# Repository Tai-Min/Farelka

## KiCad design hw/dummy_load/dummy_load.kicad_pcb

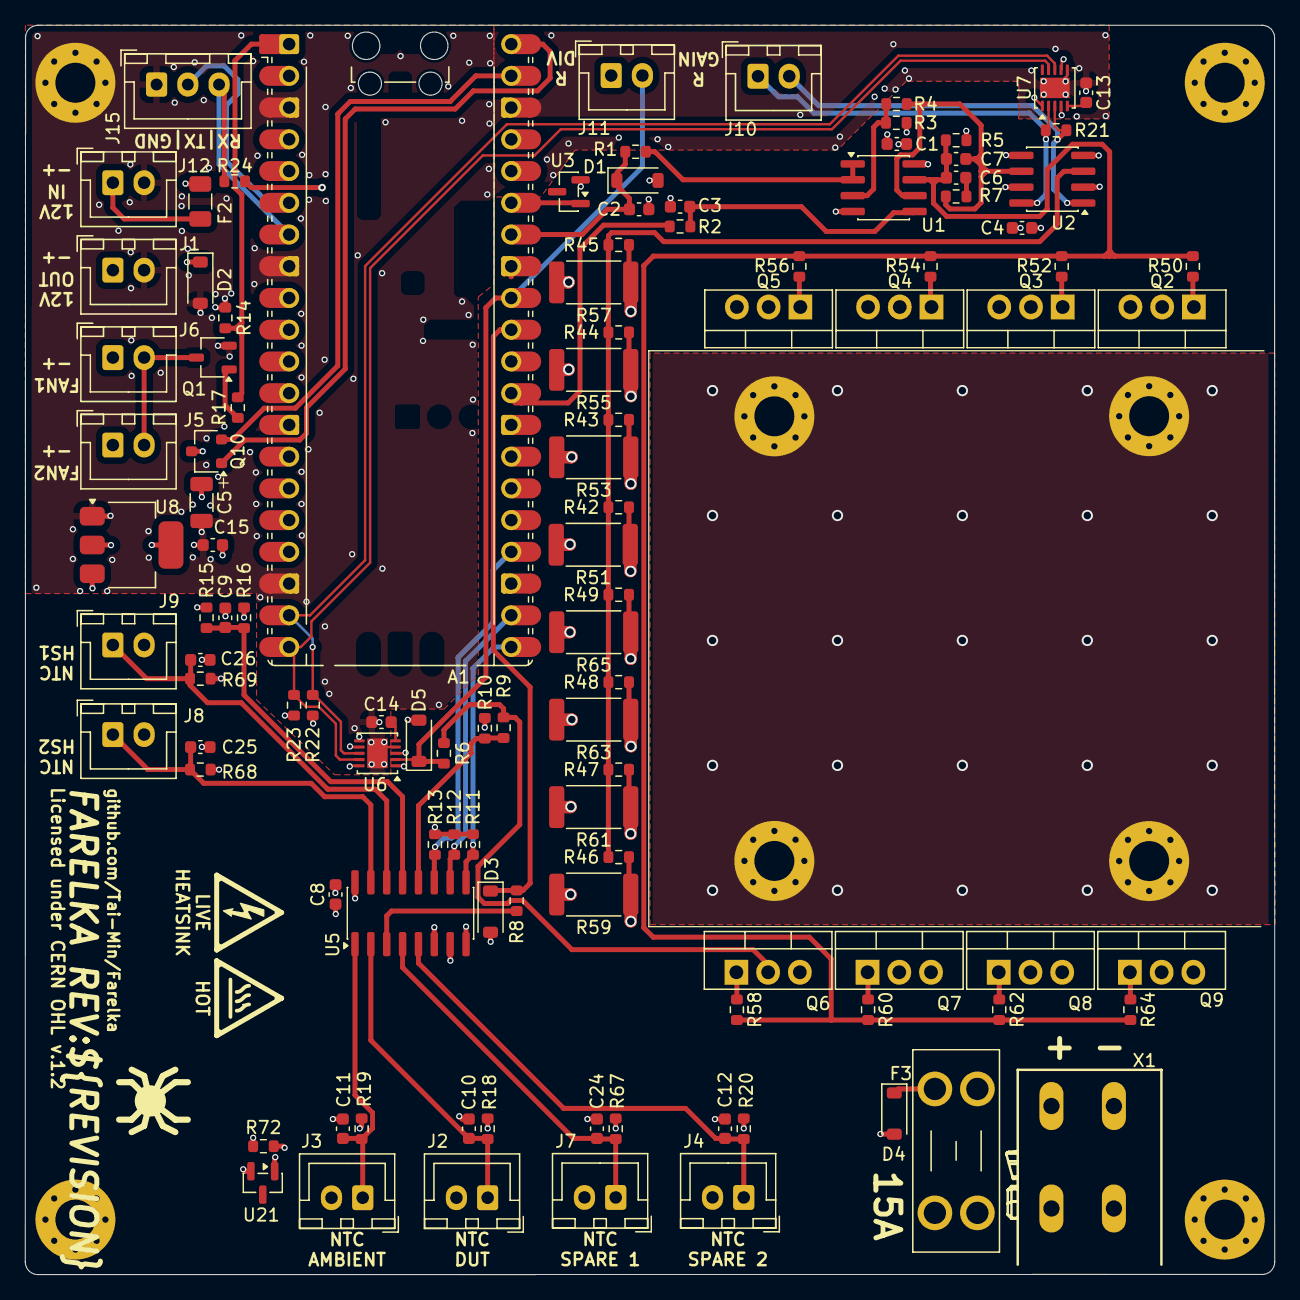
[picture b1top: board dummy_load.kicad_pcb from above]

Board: 4 copper layers, 100.0 x 100.0 mm, 115 parts (0 on the bottom side), 62 nets.

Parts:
A1: RaspberryPi_Pico; RaspberryPi_Pico_Common_Unspecified
C1, C4, C8: 100n; C_0603_1608Metric
C2, C3, C9, C10, C11, C12, C13, C14, C24, C25, C26: 1u; C_0603_1608Metric
C5: 22u; C_1206_3216Metric
C6, C7: TDB; C_0603_1608Metric
C15: 1u 50V; C_0603_1608Metric
D1, D3, D5: 3V; D_SOD-123
D2: 13V; D_SOD-123
D4: 25V; D_SOD-123
F2: 1206L300SL16ARG; Fuse_1206_3216Metric
F3: Keystone 3568; Fuseholder_Blade_Mini_Keystone_3568
H1, H2, H3, H4: MountingHole; MountingHole_3.2mm_M3_Pad_Via
HS1: SK68 50mm Fischer TO220; Heatsink
J1: 12V optional; JST_XH_B2B-XH-A_1x02_P2.50mm_Vertical
J2: NTC DUT; JST_XH_B2B-XH-A_1x02_P2.50mm_Vertical
J3: NTC Ambient; JST_XH_B2B-XH-A_1x02_P2.50mm_Vertical
J4, J7: NTC Spare; JST_XH_B2B-XH-A_1x02_P2.50mm_Vertical
J5: Fan1; JST_XH_B2B-XH-A_1x02_P2.50mm_Vertical
J6: Fan2; JST_XH_B2B-XH-A_1x02_P2.50mm_Vertical
J8, J9: NTC Heatsink; JST_XH_B2B-XH-A_1x02_P2.50mm_Vertical
J10: Calib gain; JST_XH_B2B-XH-A_1x02_P2.50mm_Vertical
J11: Calib divider; JST_XH_B2B-XH-A_1x02_P2.50mm_Vertical
J12: 12V in; JST_XH_B2B-XH-A_1x02_P2.50mm_Vertical
J15: Conn_01x03; JST_XH_B3B-XH-A_1x03_P2.50mm_Vertical
Q1: DMN2056U; TSOT-23
Q2, Q3, Q4, Q5, Q6, Q7, Q8, Q9: IRL540NPBF; TO-220-3_Vertical
Q10: DMG2305UX-7; SC-59
R1, R2: 3.3K; R_0603_1608Metric
R3, R9: 10K 1%; R_0603_1608Metric
R4, R42, R43, R44, R45, R46, R47, R48, R49: 1K 1%; R_0603_1608Metric
R5, R11, R12, R13, R14, R15, R24: 10K; R_0603_1608Metric
R6: 8.06K 1%; R_0603_1608Metric
R7, R21: TBD; R_0603_1608Metric
R8: 1K; R_0603_1608Metric
R10: 1.4K 1%; R_0603_1608Metric
R16: 3K; R_0603_1608Metric
R17, R50, R52, R54, R56, R58, R60, R62, R64: 51R; R_0603_1608Metric
R18, R19, R20, R67, R68, R69: 51K; R_0603_1608Metric
R22, R23: 4.7K; R_0603_1608Metric
R51, R53, R55, R57, R59, R61, R63, R65: 0.25R 3W 1%; R_2512_6332Metric
R72: 200R; R_0603_1608Metric
U1: LM358; SOIC-8_3.9x4.9mm_P1.27mm
U2: AD620; SOIC-8_3.9x4.9mm_P1.27mm
U3, U21: LM4040B30FTA; SOT-23
U5: 74HC4051; SOIC-16_3.9x9.9mm_P1.27mm
U6, U7: AD5272BCP; LFCSP-WD-10-1EP_3x3mm_P0.5mm_EP1.64x2.38mm
U8: AMS1117-5.0; SOT-223-3_TabPin2
X1: WAGO 2604-1102; WAGO-2604-1102

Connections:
+3.3V: A1.36 (3V3), C8.2, R11.2, R12.2, R13.2, R22.1, R23.1, R24.2, R72.2, U5.16 (VCC)
+3V0: R18.1, R19.1, R20.1, R67.1, R68.1, R69.1, R72.1, U21.1 (K)
+5V: C1.2, C4.2, C5.1, Q10.3 (D), U1.8 (V+), U2.7 (Vs+), U6.1 (VDD), U6.7 (~RESET), U6.10 (ADDR), U7.1 (VDD), U7.7 (~RESET), U8.2 (VO)
+12V: C15.2, D2.1 (K), F2.2, J1.1, J5.1, J6.1, R15.2, U8.3 (VI)
/DIGIPOT_SCL: A1.20 (GPIO15), R23.2, U6.9 (SCL), U7.9 (SCL)
/DIGIPOT_SDA: A1.19 (GPIO14), R22.2, U6.8 (SDA), U7.8 (SDA)
/DUT_SENSE: R9.1, R10.2, U5.12 (A3)
/DUT_SENSE_PRECISE: A1.32 (GPIO27_ADC1), D5.1 (K), J11.2, R6.1, U6.2 (A)
/HEATSINK_FAN_CTRL: A1.1 (GPIO0), R14.1, R17.1
/LOAD: D4.1 (K), F3.1, HS1.1, Q2.2 (D), Q3.2 (D), Q4.2 (D), Q5.2 (D), Q6.2 (D), Q7.2 (D), Q8.2 (D), Q9.2 (D), R6.2, R9.2
/LOAD_CTRL: A1.29 (GPIO22), R2.1
/LOAD_FEEDBACK: A1.34 (GPIO28_ADC2), C2.2, D1.1 (K), R1.1
/MUX_A: A1.31 (GPIO26_ADC0), D3.1 (K), R8.2
/MUX_S0: A1.24 (GPIO18), R13.1, U5.11 (S0)
/MUX_S1: A1.22 (GPIO17), R12.1, U5.10 (S1)
/MUX_S2: A1.21 (GPIO16), R11.1, U5.9 (S2)
/NTC_AMBIENT: C11.2, J3.1, R19.2, U5.1 (A4)
/NTC_DUT: C10.2, J2.1, R18.2, U5.2 (A6)
/NTC_HEATSINK_1: C26.2, J9.1, R69.2, U5.14 (A1)
/NTC_HEATSINK_2: C25.2, J8.1, R68.2, U5.15 (A2)
/NTC_SPARE_1: C24.2, J7.1, R67.2, U5.4 (A7)
/NTC_SPARE_2: C12.2, J4.1, R20.2, U5.5 (A5)
/RG1: J10.1, R21.2, U2.8 (Rg), U7.2 (A)
/RG2: J10.2, R21.1, U2.1 (Rg), U7.3 (W)
/UART_RX: A1.7 (GPIO5), J15.3, R24.1
/UART_TX: A1.6 (GPIO4), J15.2
/load/LOAD_CTRL: C6.1, C7.1, R5.2, R50.2, R52.2, R54.2, R56.2, R58.2, R60.2, R62.2, R64.2, U1.7
/load/LOAD_FEEDBACK: R42.2, R43.2, R44.2, R45.2, R46.2, R47.2, R48.2, R49.2, U2.3 (+)
GND: A1.3 (GND), A1.8 (GND), A1.13 (GND), A1.18 (GND), A1.23 (GND), A1.28 (GND), A1.38 (GND), C5.2, C13.1, C14.1, C15.1, D2.2 (A), H1.1, H2.1, H3.1, H4.1, J1.2, J12.2, J15.1, Q1.2 (S), R14.2, U5.6 (~E), U5.8 (GND), U6.4 (VSS), U6.6 (GND), U6.11 (VSS), U7.4 (VSS), U7.6 (GND), U7.11 (VSS), U8.1 (GND)
GNDA: A1.33 (AGND), C1.1, C2.1, C3.1, C4.1, C8.1, C9.1, C10.1, C11.1, C12.1, C24.1, C25.1, C26.1, D1.2 (A), D3.2 (A), D4.2 (A), D5.2 (A), J2.2, J3.2, J4.2, J7.2, J8.2, J9.2, J11.1, R3.1, R5.1, R10.1, R16.1, R51.2, R53.2, R55.2, R57.2, R59.2, R61.2, R63.2, R65.2, U1.4 (V-), U2.2 (-), U2.4 (Vs-), U2.5 (Ref), U3.2 (A), U5.7 (VEE), U6.3 (W), U21.2 (A), X1.P1.1, X1.P1.2
unnamed: A1.35 (ADC_VREF), U3.1 (K)
unnamed: A1.40 (VBUS), Q10.1 (G)
unnamed: A1.39 (VSYS), Q10.2 (S)
unnamed: C6.2, R7.2
unnamed: F3.2, X1.P2.1, X1.P2.2
unnamed: J5.2, J6.2, Q1.3 (D)
unnamed: F2.1, J12.1
unnamed: Q1.1 (G), R17.2
unnamed: Q2.1 (G), R50.1
unnamed: Q2.3 (S), R42.1, R51.1
unnamed: Q3.1 (G), R52.1
unnamed: Q3.3 (S), R43.1, R53.1
unnamed: Q4.1 (G), R54.1
unnamed: Q4.3 (S), R44.1, R55.1
unnamed: Q5.1 (G), R56.1
unnamed: Q5.3 (S), R45.1, R57.1
unnamed: Q6.1 (G), R58.1
unnamed: Q6.3 (S), R46.1, R59.1
unnamed: Q7.1 (G), R60.1
unnamed: Q7.3 (S), R47.1, R61.1
unnamed: Q8.1 (G), R62.1
unnamed: Q8.3 (S), R48.1, R63.1
unnamed: Q9.1 (G), R64.1
unnamed: Q9.3 (S), R49.1, R65.1
unnamed: R3.2, R4.2, U1.3 (+)
unnamed: R1.2, U1.1, U1.2 (-)
unnamed: C3.2, R2.2, U1.5 (+)
unnamed: C7.2, R4.1, R7.1, U1.6 (-), U2.6
unnamed: C9.2, R15.1, R16.2, U5.13 (A0)
unnamed: R8.1, U5.3 (A)
unnamed: C14.2, U6.5 (EXT_CAP)
unnamed: C13.2, U7.5 (EXT_CAP)

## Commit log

2025-12-17 Add github actions from robo-bus
2025-12-17 Add hw gitignore
2025-12-17 Add dummy load initial revision
2025-12-17 Minor repo fixes
2025-12-17 Add inner layers to board2pdf.config.ini
2025-12-17 Fix digipot cap value
2025-12-17 Fix hotspot, remove old schematic file
2025-12-17 AUTO: Update reports
2025-12-17 Add dummy load initial revision (#1)
    * Add dummy load initial revision
    * Minor repo fixes
    * Add inner layers to board2pdf.config.ini
    * Fix digipot cap value
    * Fix hotspot, remove old schematic file
    ---------
2025-12-17 Replace terminal block, update BOM and datasheets, minor fixes to tracing
2025-12-17 Replace terminal block, update BOM and datasheets, minor fixes to tracing (#2)
2025-12-17 Add hardware license
2025-12-17 Add hardware license (#3)
2025-12-17 Add license on silkscreen
2025-12-17 Add more vias
2025-12-18 Add license on silkscreen (#5)
    * Add license on silkscreen
    * Add more vias
    ---------
2025-12-22 Better PCB design, update BOM, add UART header for debugging
2025-12-22 Better PCB design, update BOM, add UART header for debugging (#7)

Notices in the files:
hw/dummy_load/dummy_load.kicad_pcb:
Licensed under CERN OHL v.1.2
